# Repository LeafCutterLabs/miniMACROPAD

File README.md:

# miniMACROPAD
A programable 4-button keypad/macropad based on attiny85 with mechanical switches.
To utilize all four inputs you will need to set the fuses for P5 and remove the LED from P1. See https://www.youtube.com/watch?v=JENvbYm0iJ8

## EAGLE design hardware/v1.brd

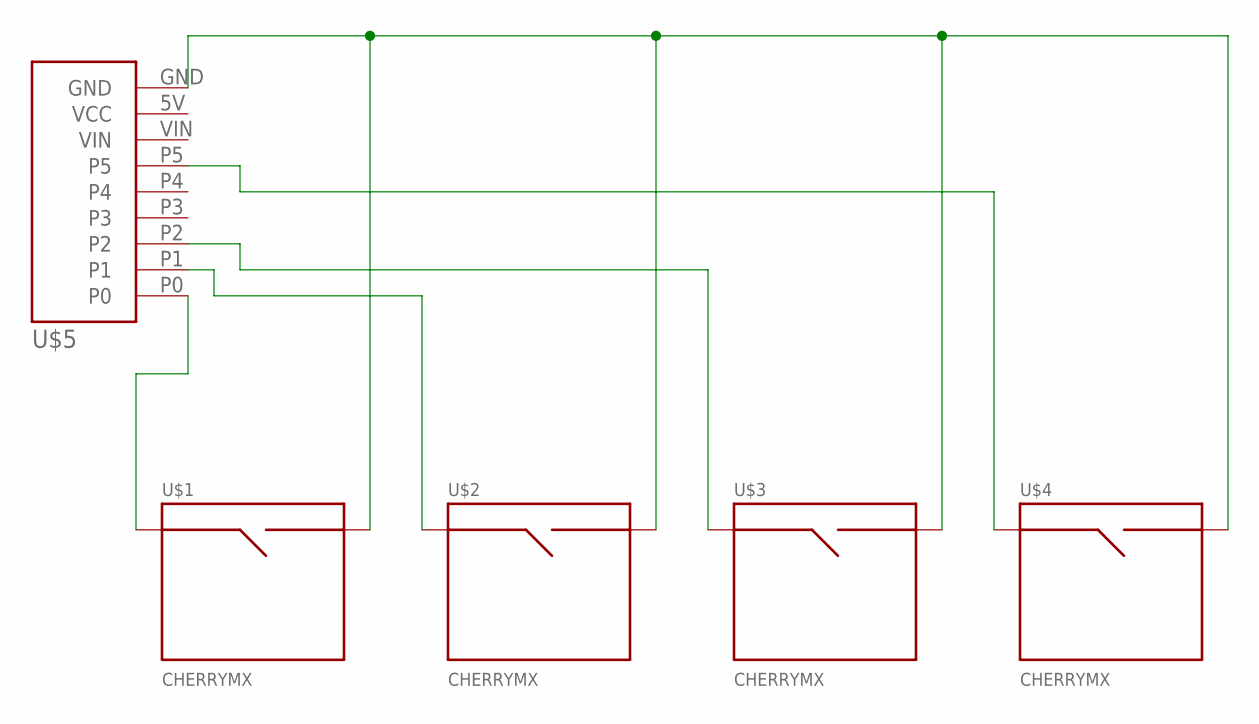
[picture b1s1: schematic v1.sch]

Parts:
U$1, U$2, U$3, U$4: CHERRYMX
U$5: ATTINY85

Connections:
GND: U$1.P$2 (SIG2), U$2.P$2 (SIG2), U$3.P$2 (SIG2), U$4.P$2 (SIG2), U$5.GND
unnamed: U$1.P$1 (SIG1), U$5.P0
unnamed: U$2.P$1 (SIG1), U$5.P1
unnamed: U$3.P$1 (SIG1), U$5.P2
unnamed: U$4.P$1 (SIG1), U$5.P5

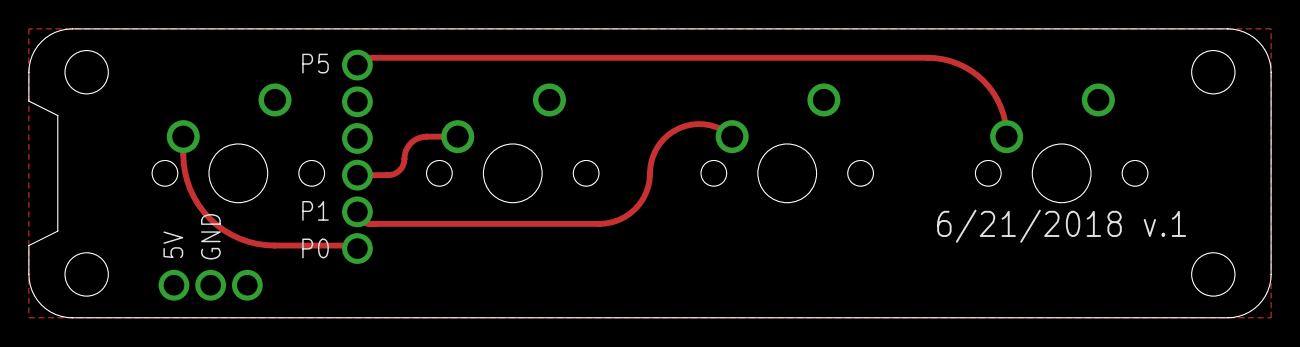
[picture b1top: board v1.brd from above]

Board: 2 copper layers, 86.0 x 20.0 mm, 5 parts (0 on the bottom side), 5 nets.

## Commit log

2018-07-16 Create placeholder
